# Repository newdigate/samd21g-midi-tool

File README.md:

# Midi Tool
[kicad](https://www.kicad.org/) design files for a general purpose midi dev board based on Arduino MKRZero 

* [samdg21](https://www.microchip.com/en-us/product/atsamd21g18) arm cortex m0 microcontroller
* DIN-5 midi input and output
* st7735 display (128x128 16bit)
* [PCF8523T](https://www.nxp.com/part/PCF8523T) realtime clock RTC
* socket for micro-SD card
* status LED
* SWD connection for programming
* PJ-320A connector for 2 foot-switches
* 5V POWER via USB
* 3V3 regulator
* 4-pin socket for neopixel strip
* Status LED

## Firmware
 * [samd21g-midi-tool-software](https://github.com/newdigate/samd21g-midi-tool-software)
   
## Kicad plugins
 * [JLCPCB](https://github.com/Bouni/kicad-jlcpcb-tools)
 * [Freerouting](https://github.com/freerouting/freerouting)

## Arduino libraries
* [PCF8523](https://github.com/SpellFoundry/PCF8523)
* [Adafruit-ST7735-Library](https://github.com/adafruit/Adafruit-ST7735-Library)
* [arduino_midi_library](https://github.com/FortySevenEffects/arduino_midi_library)

## sources / credits:
  * schematics and pcb design based on [MKRZERO Arduino](https://docs.arduino.cc/hardware/mkr-zero/)   
  * 3d models:
    * [PJ320A PJ320D 3.5mm JACK](https://grabcad.com/library/pj320a-pj320d-3-5mm-jack-1)
    * [SMD CR1220 Battery case](https://grabcad.com/library/smd-cr1220-battery-case-1)
  * footprints
    * [PJ-320A](https://github.com/nathanhborger/PJ-320A_KiCad_Library)

## images

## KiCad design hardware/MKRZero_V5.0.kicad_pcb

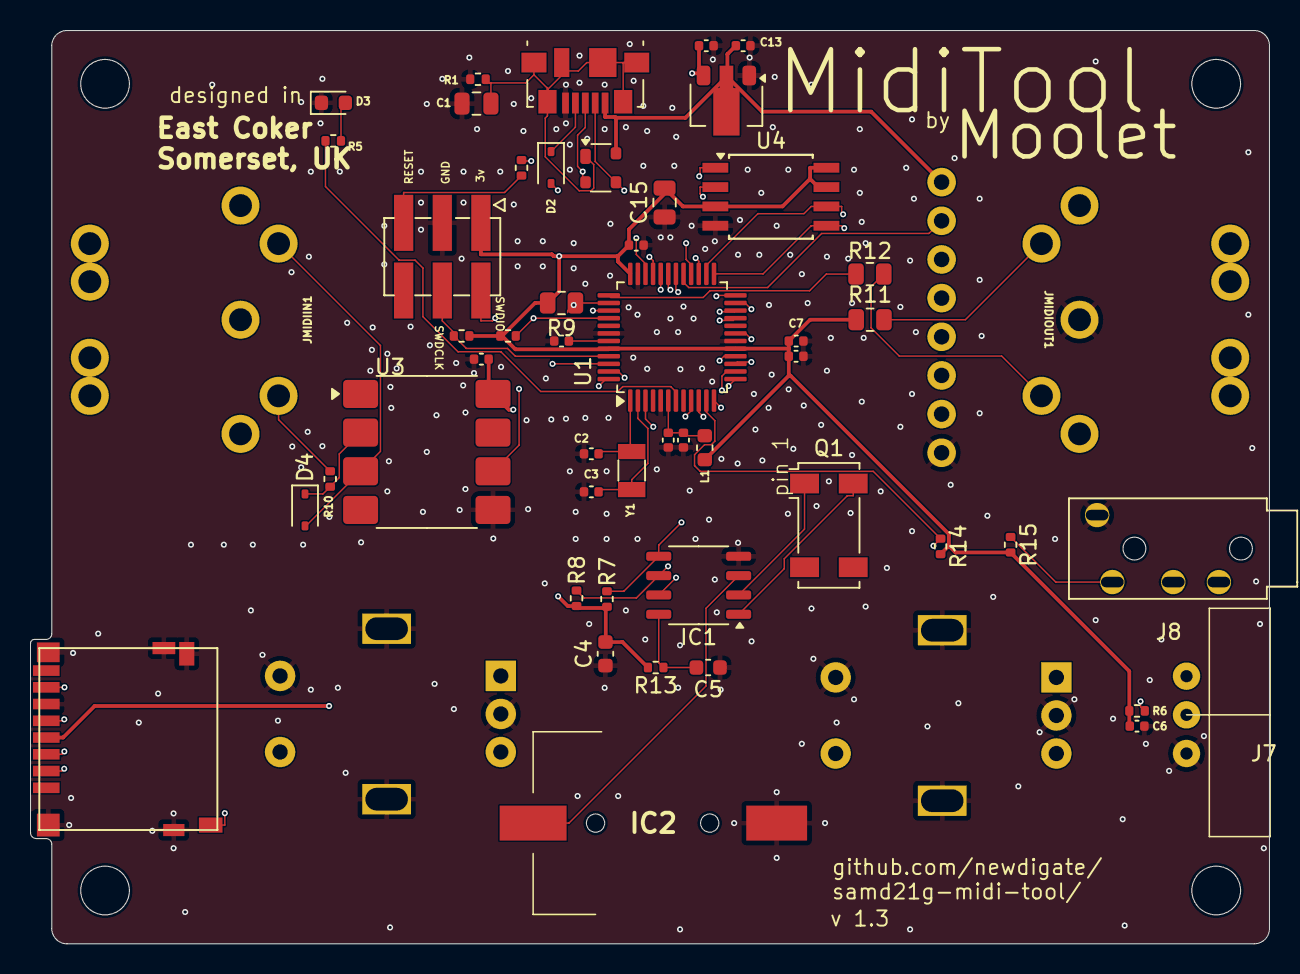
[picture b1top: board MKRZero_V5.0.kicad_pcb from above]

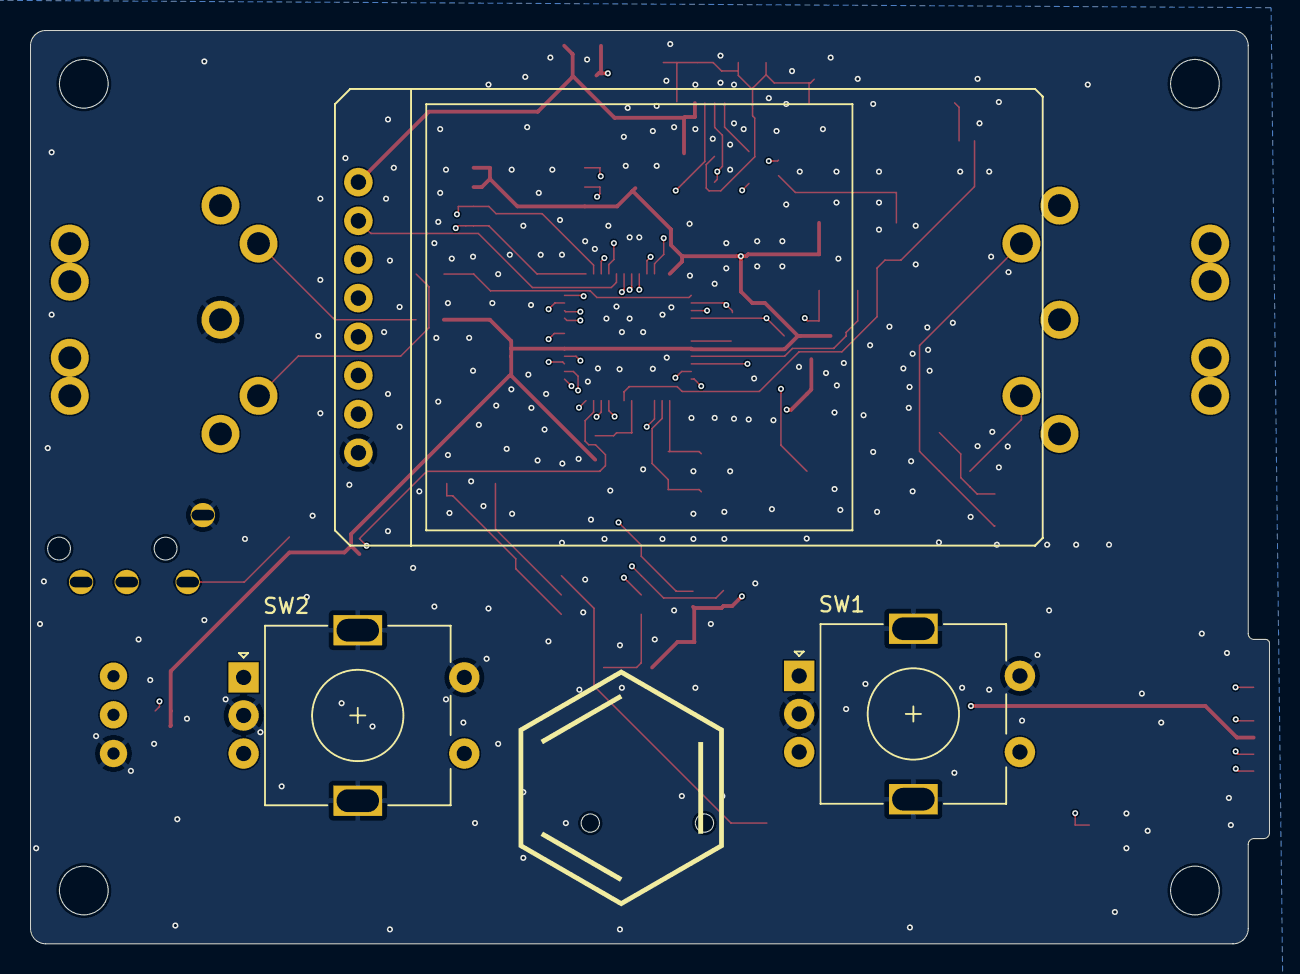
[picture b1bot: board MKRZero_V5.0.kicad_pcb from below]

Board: 4 copper layers, 81.4 x 60.0 mm, 58 parts (3 on the bottom side), 53 nets.

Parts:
C1: 4.7nF; C_0805_2012Metric
C2, C3: 20pF; C_0402_1005Metric
C4, C5: 10uF; C_0603_1608Metric
C6, C7, C9, C10, C11, C16: 100nF; C_0402_1005Metric
C8, C13, C14: 1uF; C_0402_1005Metric
C12: 4.7uF; C_0402_1005Metric
C15: .1uF; C_0805_2012Metric
D1: PRTR5V0U2X,215; SOT-143
D2: PMEG2005EL; D_SOD-323
D3: LED; LED_0603_1608Metric
D4: 1N4148; D_SOD-323
H1, H2, H3, H4: MountingHole; MountingHole_3.2mm_M3
IC1: PCF8523T; SOP-8_3.9x4.9mm_P1.27mm
IC2: CR1220-2; CR12202
J1: USB_B_Micro; USB_Micro-B_Molex_47346-0001
J2: 2X3_SMD_MALE; 2X3_SMT
J3: AMPHENOL_114-00841-68
J6: Conn_01x08_Pin; ST7735
J7: Conn_01x03_Pin; MG03254F-RA
J8: PJ-320A
JMIDIIN1: DIN-5; Deltron-671-0501-5
JMIDIOUT1: DIN-5; Deltron-671-0501-5
L1: BLM18PG471SN1D; L_0603_1608Metric
Q1: 32.768KHz; Crystal_SMD_Abracon_ABS25-4Pin_8.0x3.8mm
R1: 1M; R_0402_1005Metric
R2: 39; R_0402_1005Metric
R3, R13: 1K; R_0402_1005Metric
R4: 10K; R_0402_1005Metric
R5: 330; R_0402_1005Metric
R6: 100k; R_0402_1005Metric
R7, R8, R14, R15: 10k; R_0402_1005Metric
R9: 470; R_0805_2012Metric
R10: 220; R_0402_1005Metric
R11, R12: 47; R_0805_2012Metric
SW1, SW2: RotaryEncoder_Switch_MP; RotaryEncoder_Alps_EC11E-Switch_Vertical_H20mm
U1: ATSAMD21G18A-48; TQFP-48_7x7mm_P0.5mm
U2: AP7215-33YG-13; SOT-89-3
U3: 6N138; SOP-8_6.605x9.655mm_P2.54mm
U4: W25Q128JVS; SOIC-8W_5.3x5.3mm_P1.27mm
Y1: 32.768KHz; Crystal_SMD_3215-2Pin_3.2x1.5mm

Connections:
+3V3: C4.2, C6.1, C7.1, C9.1, C10.2, C14.2, C15.2, J2.1, J3.4 (VDD), L1.1, R3.1, R4.1, R6.2, R7.2, R8.2, R9.2, R11.1, R13.2, R14.2, R15.2, U1.17 (VDDIO@1), U1.36 (VDDIO@2), U1.44 (VDDIN), U2.3 (VROUT), U4.3 (IO2), U4.7 (IO3), U4.8 (VCC)
+5V: C13.2, C16.2, D1.4 (VCC), J1.1 (VBUS), J6.2, J6.8, J7.1, U2.2 (VIN), U3.8 (VCC)
/PA00_XIN32: C2.2, U1.1 (PA00/XIN32), Y1.2
/PA01_XOUT32: C3.2, U1.2 (PA01/XOUT32), Y1.1
/PA02_AIN0: SW2.B, U1.3 (PA02)
/PA04_AIN4: SW1.B, U1.9 (PA04)
/PA05_AIN5: J8.2 (Tip), R15.1, U1.10 (PA05)
/PA06_AIN6: J8.3 (Ring1), R14.1, U1.11 (PA06)
/PA07_AIN7: IC1.7 (~INT1/CLKOUT), U1.12 (PA07)
/PA08_S0_I2C_SDA: IC1.5 (SDA), R7.1, U1.13 (PA08)
/PA09_S0_I2C_SCL: IC1.6 (SCL), R8.1, U1.14 (PA09)
/PA10_TCC0-W2: J6.6, U1.15 (PA10)
/PA11_TCC0-W3: SW1.S1, U1.16 (PA11)
/PA12_S2_MOSI: J3.3 (CMD), U1.21 (PA12)
/PA13_S2_SCK: J3.5 (CLK), U1.22 (PA13)
/PA14_S2_NSS: J3.2 (CD/DAT3), R6.1, U1.23 (PA14)
/PA15_S2_MISO: J3.7 (DAT0), U1.24 (PA15)
/PA16_S1_MOSI: J6.4, U1.25 (PA16), U4.5 (DI(IO0))
/PA17_S1_SCK: J6.3, U1.26 (PA17), U4.6 (CLK)
/PA18_USB_ID: D2.2 (A), U1.27 (PA18)
/PA19_S1_MISO: U1.28 (PA19), U4.2 (DO(IO1))
/PA20_TCC0-W6: J6.7, U1.29 (PA20)
/PA21_TCC0-W7: SW1.A, U1.30 (PA21)
/PA22_TC4-W0: J7.2, U1.31 (PA22)
/PA23_TC4-W1: J6.5, U1.32 (PA23)
/PA27_CD: J3.CD1, U1.39 (PA27)
/PA30_SWCLK: J2.4, R3.2, U1.45 (PA30/SWCLK)
/PA31_SWDIO: J2.2, U1.46 (PA31/SWDIO)
/PB02_AIN10: SW2.S1, U1.47 (PB02)
/PB03_AIN11: U1.48 (PB03), U4.1 (~CS)
/PB08_LED: R5.2, U1.7 (PB08)
/PB10_TCC0-W4: SW2.A, U1.19 (PB10)
/PB22_S5_TX: R12.2, U1.37 (PB22)
/PB23_S5_RX: R9.1, U1.38 (PB23), U3.6 (VO2)
/RESETN: R2.2, R4.2, U1.40 (RESETN)
/USB_N: D1.3 (I/O2), J1.2 (D-), U1.33 (PA24/USB_DM)
/USB_P: D1.2 (I/O1), J1.3 (D+), U1.34 (PA25/USB_DP)
GND: C1.2, C2.1, C3.1, C4.1, C5.1, C6.2, C7.2, C8.2, C9.2, C10.1, C11.2, C12.2, C13.1, C14.1, C15.1, C16.1, D3.1 (K), IC1.4 (VSS), IC2.1, J1.5 (GND), J2.3, J3.6 (VSS), J3.CD2, J3.SH1 (G3), J3.SH2 (G3), J3.SH3 (G2), J3.SH4 (G2), J6.1, J7.3, J8.1 (Sleeve), JMIDIOUT1.2, R1.2, SW1.C, SW1.MP, SW1.S2, SW2.C, SW2.MP, SW2.S2, U1.5 (GNDANA), U1.18 (GND@1), U1.35 (GND@2), U1.42 (GND@3), U2.1 (GND), U3.5 (GND), U4.4 (GND)
unnamed: C1.1, D1.1 (GND), J1.6 (Shield), R1.1
unnamed: D2.1 (K), J1.4 (ID)
unnamed: D3.2 (A), R5.1
unnamed: D4.2 (A), JMIDIIN1.5, U3.3 (C2)
unnamed: D4.1 (K), R10.2, U3.2 (C1)
unnamed: IC1.1 (OSCI), Q1.4 (e)
unnamed: IC1.2 (OSCO), Q1.1
unnamed: IC1.3 (VBAT), IC2.2
unnamed: C5.2, IC1.8 (VDD), R13.1
unnamed: J2.5, R2.1
unnamed: JMIDIIN1.4, R10.1
unnamed: JMIDIOUT1.4, R11.2
unnamed: JMIDIOUT1.5, R12.1
unnamed: C11.1, C12.1, L1.2, U1.6 (VDDANA)
unnamed: C8.1, U1.43 (VDDCORE)

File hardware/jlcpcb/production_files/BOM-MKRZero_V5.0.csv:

Comment,Designator,Footprint,LCSC
1K,"R13,R3",R_0402_1005Metric,C11702
"PRTR5V0U2X,215",D1,SOT-143,C12333
USB_B_Micro,J1,USB_Micro-B_Molex_47346-0001,C132560
.1uF,C15,C_0805_2012Metric,C150376
100nF,"C10,C11,C16,C6,C7,C9",C_0402_1005Metric,C1525
20pF,"C2,C3",C_0402_1005Metric,C1554
4.7nF,C1,C_0805_2012Metric,C1744
470,R9,R_0805_2012Metric,C17710
47,"R11,R12",R_0805_2012Metric,C17714
PMEG2005EL,D2,D_SOD-323,C179428
32.768KHz,Q1,Crystal_SMD_Abracon_ABS25-4Pin_8.0x3.8mm,C179637
6N138,U3,SOP-8_6.605x9.655mm_P2.54mm,C188666
10uF,"C4,C5",C_0603_1608Metric,C19702
DIN-5,"JMIDIIN1,JMIDIOUT1",Deltron-671-0501-5,C20611696
1N4148,D4,D_SOD-323,C2128
LED,D3,LED_0603_1608Metric,C2286
4.7uF,C12,C_0402_1005Metric,C23733
220,R10,R_0402_1005Metric,C25091
10k,"R14,R15,R5",R_0402_1005Metric,C25104
39,R2,R_0402_1005Metric,C25109
100k,R6,R_0402_1005Metric,C25741
10K,"R4,R7,R8",R_0402_1005Metric,C25744
1M,R1,R_0402_1005Metric,C26083
PCF8523T,IC1,SOP-8_3.9x4.9mm_P1.27mm,C2651516
AMPHENOL_114-00841-68,J3,AMPHENOL_114-00841-68,C2848817
PJ-320A,J8,PJ-320A,C2884984
32.768KHz,Y1,Crystal_SMD_3215-2Pin_3.2x1.5mm,C32346
2X3_SMD_MALE,J2,2X3_SMT,C3294461
RotaryEncoder_Switch_MP,SW1,RotaryEncoder_Alps_EC11E-Switch_Vertical_H20mm,C361165
AP7215-33YG-13,U2,SOT-89-3,C460367
1uF,"C13,C14,C8",C_0402_1005Metric,C52923
ATSAMD21G18A-48,U1,TQFP-48_7x7mm_P0.5mm,C78624
BLM18PG471SN1D,L1,L_0603_1608Metric,C97853
Conn_01x03_Pin,J7,MG03254F-RA,
Conn_01x08_Pin,J6,ST7735,
RotaryEncoder_Switch_MP,SW2,RotaryEncoder_Alps_EC11E-Switch_Vertical_H20mm,
CR1220-2,IC2,CR12202,
W25Q128JVS,U4,SOIC-8W_5.3x5.3mm_P1.27mm,

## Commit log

2024-08-26 images
2024-08-26 schematic images
2024-08-26 correction to battery holder footprint
2024-08-31 add second pair of mounting holes for DIN5 midi connector socket to make compatible with different DIN5 variations
2024-10-02 midi connector corrections, use MG03254F-RA magnetic pogo 3pin connector
2024-11-02 midi still not working
2024-11-03 v1.3 hopefully midi in will work this time?
